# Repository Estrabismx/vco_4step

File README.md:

# vco_4step
Oscilador controlado por voltaje de 4 pasos

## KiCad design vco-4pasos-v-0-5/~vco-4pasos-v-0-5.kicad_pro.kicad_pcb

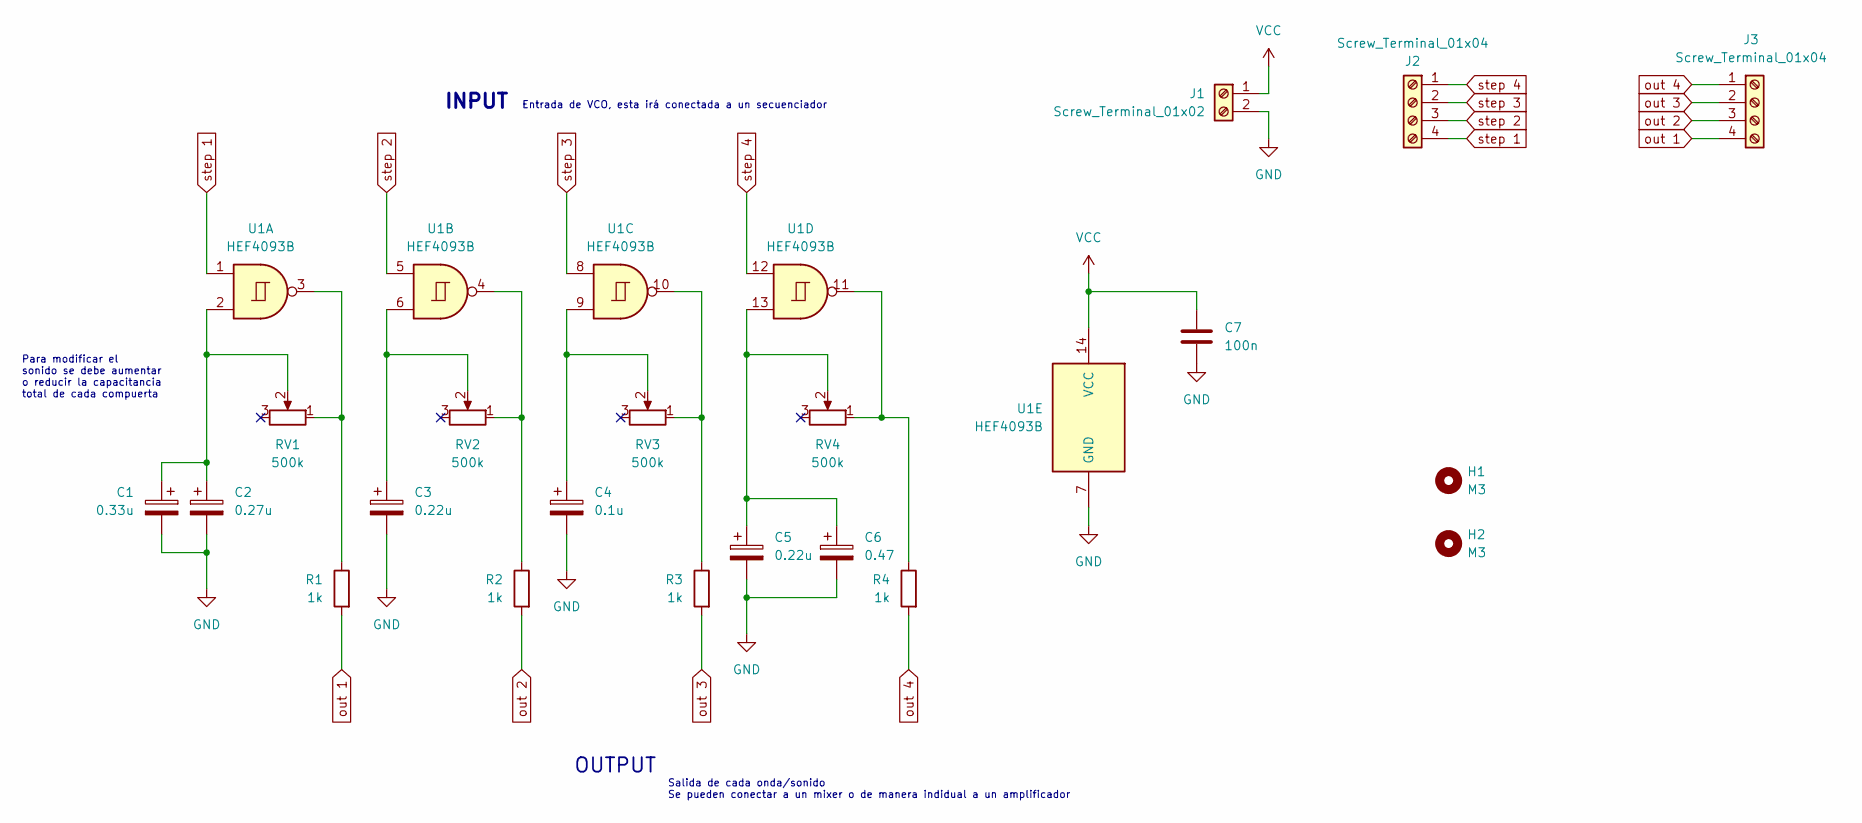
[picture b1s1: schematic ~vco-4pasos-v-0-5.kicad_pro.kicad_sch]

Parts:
C1: 0.33u; CP_Radial_D4.0mm_P2.00mm
C2: 0.27u; CP_Radial_D4.0mm_P2.00mm
C3, C5: 0.22u; CP_Radial_D4.0mm_P2.00mm
C4: 0.1u; CP_Radial_D4.0mm_P2.00mm
C6: 0.47; CP_Radial_D4.0mm_P2.00mm
C7: 100n; C_Disc_D5.0mm_W2.5mm_P2.50mm
H1, H2: M3; MountingHole_3.2mm_M3
J1: Screw_Terminal_01x02; TerminalBlock_Xinya_XY308-2.54-2P_1x02_P2.54mm_Horizontal
J2, J3: Screw_Terminal_01x04; TerminalBlock_Xinya_XY308-2.54-4P_1x04_P2.54mm_Horizontal
R1, R2, R3, R4: 1k; R_Axial_DIN0207_L6.3mm_D2.5mm_P10.16mm_Horizontal
RV1, RV2, RV3, RV4: 500k; TerminalBlock_Xinya_XY308-2.54-2P_1x02_P2.54mm_Horizontal
U1: HEF4093B; DIP-14_W7.62mm_LongPads

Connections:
GND: C1.2, C2.2, C3.2, C4.2, C5.2, C6.2, C7.2, J1.2, U1.7 (GND)
unnamed: C1.1, C2.1, RV1.2, U1.2
unnamed: C3.1, RV2.2, U1.6
unnamed: C4.1, RV3.2, U1.9
unnamed: C5.1, C6.1, RV4.2, U1.13
unnamed: R1.1, RV1.1, U1.3
unnamed: R2.1, RV2.1, U1.4
unnamed: R3.1, RV3.1, U1.10
unnamed: R4.1, RV4.1, U1.11
VCC: C7.1, J1.1, U1.14 (VCC)
out 1: J3.4, R1.2
out 2: J3.3, R2.2
out 3: J3.2, R3.2
out 4: J3.1, R4.2
step 1: J2.4, U1.1
step 2: J2.3, U1.5
step 3: J2.2, U1.8
step 4: J2.1, U1.12

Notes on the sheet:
Salida de cada onda/sonido Se pueden conectar a un mixer o de manera indidual a un amplificador
INPUT
Entrada de VCO, esta irá conectada a un secuenciador
OUTPUT
Para modificar el sonido se debe aumentar o reducir la capacitancia total de cada compuerta

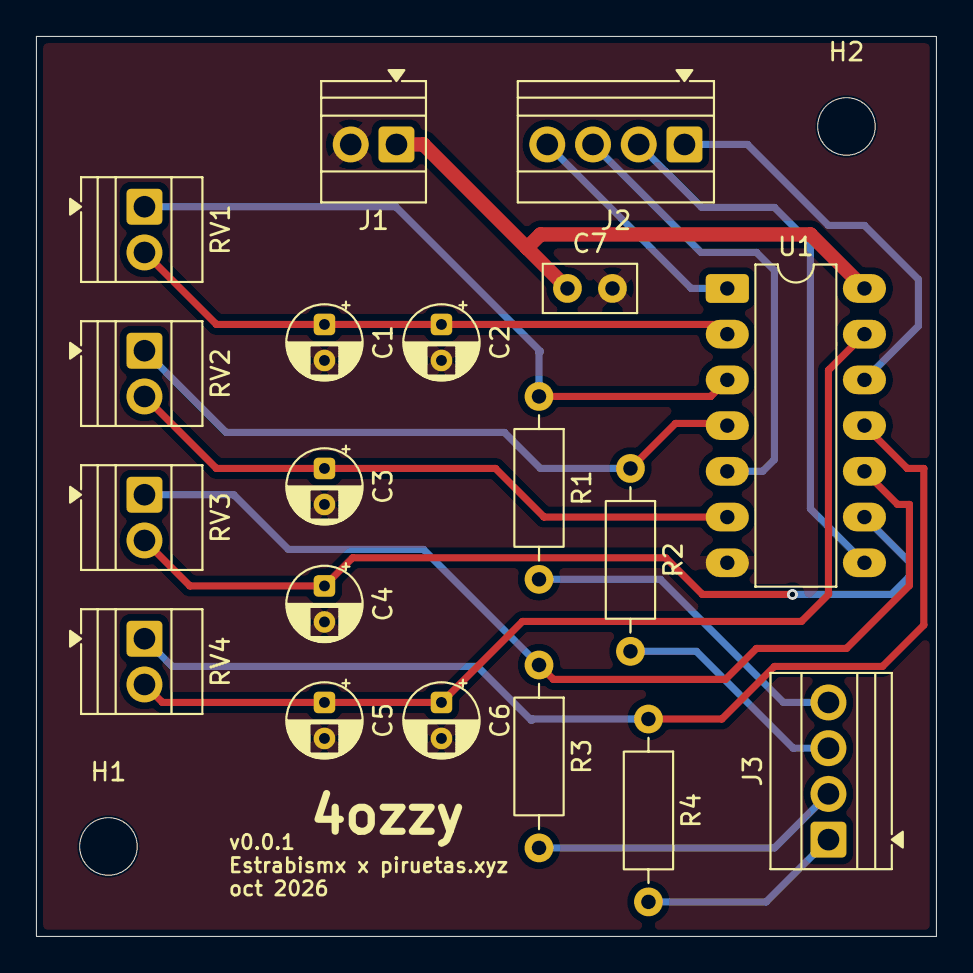
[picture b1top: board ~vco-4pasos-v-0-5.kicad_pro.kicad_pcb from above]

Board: 2 copper layers, 50.0 x 50.0 mm, 21 parts (0 on the bottom side), 18 nets.
